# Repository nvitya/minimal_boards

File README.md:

# Breadboard Friendly Minimal Boards

The project on the Github: [https://github.com/nvitya/minimal_boards](https://github.com/nvitya/minimal_boards)

The boards are developed with KiCAD 5: [http://kicad.org/](http://kicad.org/)

## Board List

__Name__        | __Status__      | __Description__
----------------|-----------------|-------------------------------------------------------------
MIBO48-STM32    | Tested, OK      | For 48 pin QFP STM32 Microcontrollers (F103, F303, F070 etc)
MIBO48-STM32G4  | Tested, OK      | For 48 pin QFP STM32G4 Microcontrollers
MIBO48-XMC4     | Tested, OK      | For 48 pin QFP XMC4000 Microcontrollers
MIBO64-STM32    | Tested, OK      | For 64 pin QFP STM32 Microcontrollers (F405, F303, F070 etc)
MIBO64-ATSAM4S  | Tested, OK      | For 64 pin QFP ATSAM4SxB Microcontrollers
MIBO64-ATSAME5X | Tested, OK      | For 64 pin QFP ATSAME5xJ/ATSAMD5x Microcontrollers
MIBO20-STM32    | Tested, OK      | For the 20 pin TSSOP STM32 Microcontrollers (F030, F070, L011 etc)

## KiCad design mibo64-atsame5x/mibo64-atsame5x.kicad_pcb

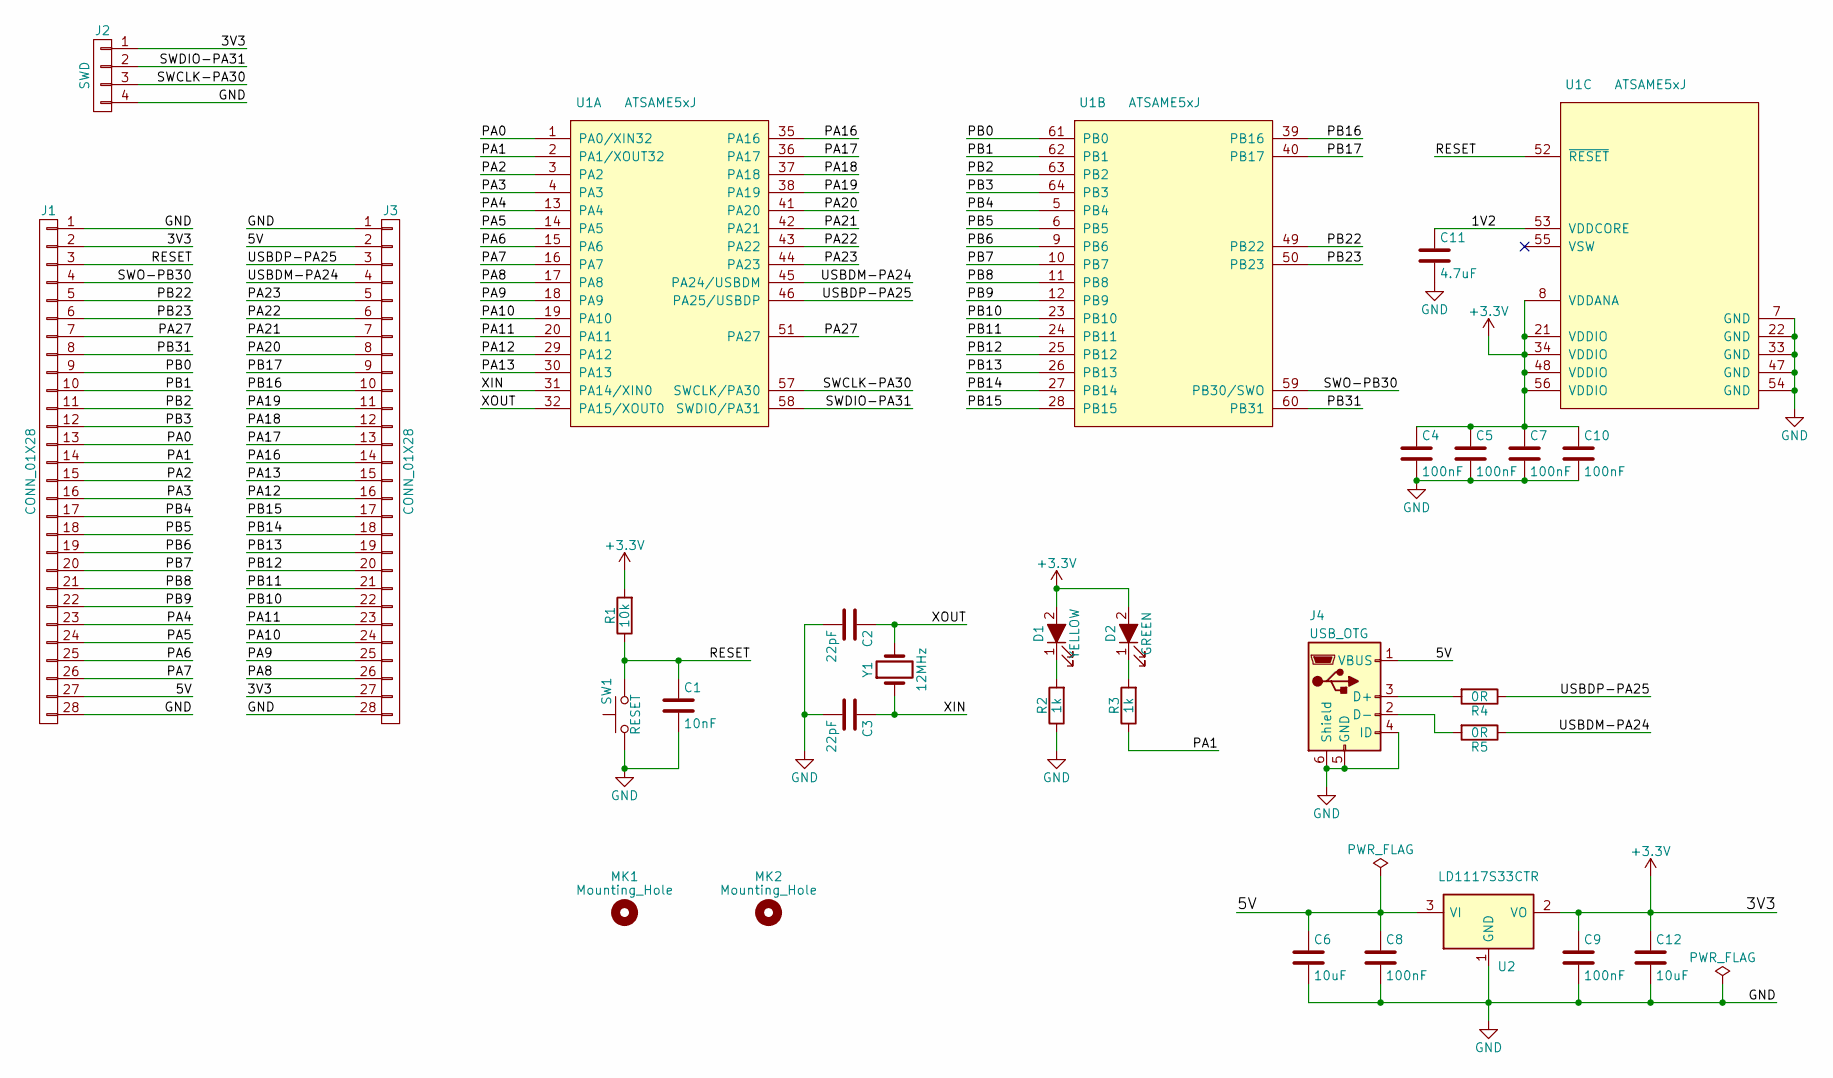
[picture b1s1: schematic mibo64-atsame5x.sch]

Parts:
C1: 10nF; C_0603_HandSoldering
C2, C3: 22pF; C_0603_HandSoldering
C4, C5, C7, C8, C9, C10: 100nF; C_0603_HandSoldering
C6, C12: 10uF; C_0603_HandSoldering
C11: 4.7uF; C_0603_HandSoldering
D1: YELLOW; LED_0603_HandSoldering
D2: GREEN; LED_0603_HandSoldering
J1, J3: CONN_01X28; Pin_Header_Straight_1x28_Pitch2.54mm
J2: SWD; Pin_Header_Straight_1x04_Pitch2.54mm
J4: USB_OTG; USB_Micro-B
MK1, MK2: Mounting_Hole; MountingHole_3.2mm_M3
R1: 10k; R_0603_HandSoldering
R2, R3: 1k; R_0603_HandSoldering
R4, R5: 0R; R_0603_HandSoldering
SW1: RESET; SW_SPST_FSMSM
U1: ATSAME5xJ; TQFP-64_10x10mm_Pitch0.5mm
U2: LD1117S33CTR; SOT-223
Y1: 12MHz; Crystal_HC49-4H_Vertical

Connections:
+3V3: C4.1, C5.1, C7.1, C9.1, C10.1, C12.1, D1.2 (A), D2.2 (A), J1.2, J2.1, J3.27, R1.2, U1.8 (VDDANA), U1.21 (VDDIO), U1.34 (VDDIO), U1.48 (VDDIO), U1.56 (VDDIO), U2.2 (VO)
/1V2: C11.1, U1.53 (VDDCORE)
/5V: C6.1, C8.1, J1.27, J3.2, J4.1 (VBUS), U2.3 (VI)
/PA0: J1.13, U1.1 (PA0/XIN32)
/PA1: J1.14, R3.1, U1.2 (PA1/XOUT32)
/PA2: J1.15, U1.3 (PA2)
/PA3: J1.16, U1.4 (PA3)
/PA4: J1.23, U1.13 (PA4)
/PA5: J1.24, U1.14 (PA5)
/PA6: J1.25, U1.15 (PA6)
/PA7: J1.26, U1.16 (PA7)
/PA8: J3.26, U1.17 (PA8)
/PA9: J3.25, U1.18 (PA9)
/PA10: J3.24, U1.19 (PA10)
/PA11: J3.23, U1.20 (PA11)
/PA12: J3.16, U1.29 (PA12)
/PA13: J3.15, U1.30 (PA13)
/PA16: J3.14, U1.35 (PA16)
/PA17: J3.13, U1.36 (PA17)
/PA18: J3.12, U1.37 (PA18)
/PA19: J3.11, U1.38 (PA19)
/PA20: J3.8, U1.41 (PA20)
/PA21: J3.7, U1.42 (PA21)
/PA22: J3.6, U1.43 (PA22)
/PA23: J3.5, U1.44 (PA23)
/PA27: J1.7, U1.51 (PA27)
/PB0: J1.9, U1.61 (PB0)
/PB1: J1.10, U1.62 (PB1)
/PB2: J1.11, U1.63 (PB2)
/PB3: J1.12, U1.64 (PB3)
/PB4: J1.17, U1.5 (PB4)
/PB5: J1.18, U1.6 (PB5)
/PB6: J1.19, U1.9 (PB6)
/PB7: J1.20, U1.10 (PB7)
/PB8: J1.21, U1.11 (PB8)
/PB9: J1.22, U1.12 (PB9)
/PB10: J3.22, U1.23 (PB10)
/PB11: J3.21, U1.24 (PB11)
/PB12: J3.20, U1.25 (PB12)
/PB13: J3.19, U1.26 (PB13)
/PB14: J3.18, U1.27 (PB14)
/PB15: J3.17, U1.28 (PB15)
/PB16: J3.10, U1.39 (PB16)
/PB17: J3.9, U1.40 (PB17)
/PB22: J1.5, U1.49 (PB22)
/PB23: J1.6, U1.50 (PB23)
/PB31: J1.8, U1.60 (PB31)
/RESET: C1.1, J1.3, R1.1, SW1.2, U1.52 (~RESET)
/SWCLK-PA30: J2.3, U1.57 (SWCLK/PA30)
/SWDIO-PA31: J2.2, U1.58 (SWDIO/PA31)
/SWO-PB30: J1.4, U1.59 (PB30/SWO)
/USBDM-PA24: J3.4, R5.1, U1.45 (PA24/USBDM)
/USBDP-PA25: J3.3, R4.1, U1.46 (PA25/USBDP)
/XIN: C3.1, U1.31 (PA14/XIN0), Y1.1
/XOUT: C2.1, U1.32 (PA15/XOUT0), Y1.2
GND: C1.2, C2.2, C3.2, C4.2, C5.2, C6.2, C7.2, C8.2, C9.2, C10.2, C11.2, C12.2, J1.1, J1.28, J2.4, J3.1, J3.28, J4.4 (ID), J4.5 (GND), J4.6 (Shield), R2.1, SW1.1, U1.7 (GND), U1.22 (GND), U1.33 (GND), U1.47 (GND), U1.54 (GND), U2.1 (GND)
unnamed: D1.1 (K), R2.2
unnamed: D2.1 (K), R3.2
unnamed: J4.2 (D-), R5.2
unnamed: J4.3 (D+), R4.2

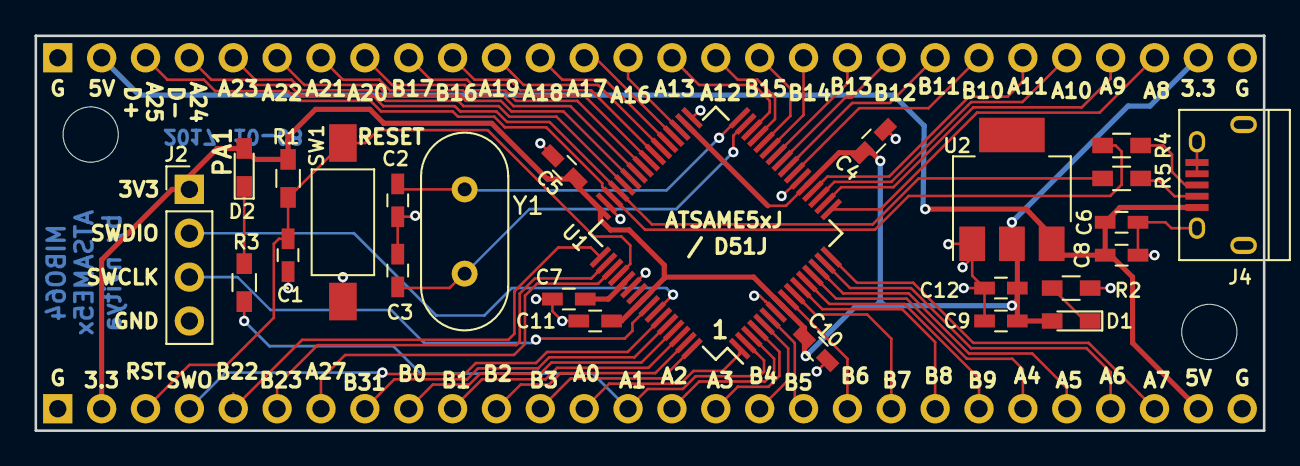
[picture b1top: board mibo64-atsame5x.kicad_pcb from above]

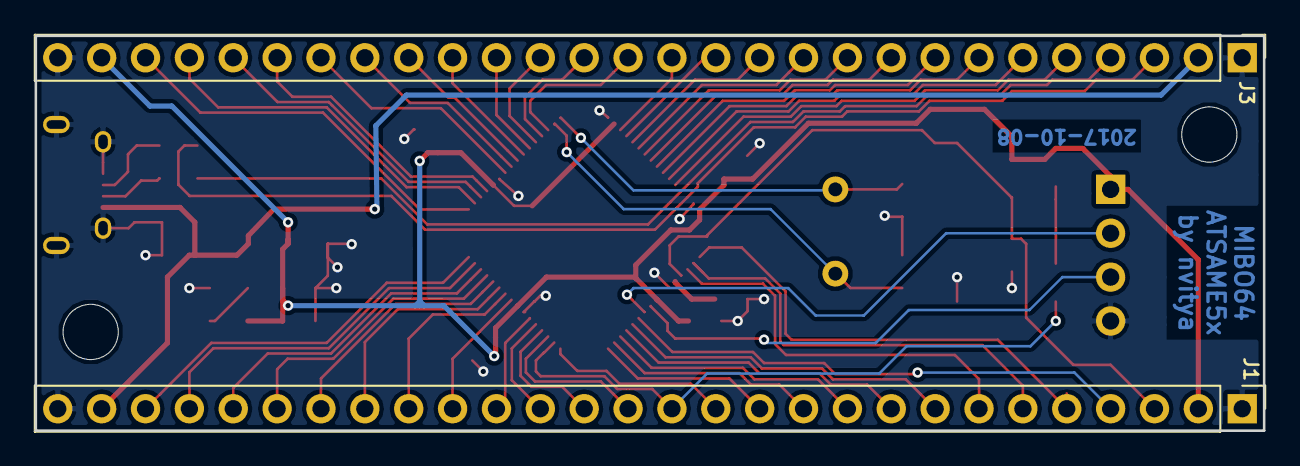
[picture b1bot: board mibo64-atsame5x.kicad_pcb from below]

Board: 2 copper layers, 71.1 x 22.9 mm, 29 parts (2 on the bottom side), 60 nets.

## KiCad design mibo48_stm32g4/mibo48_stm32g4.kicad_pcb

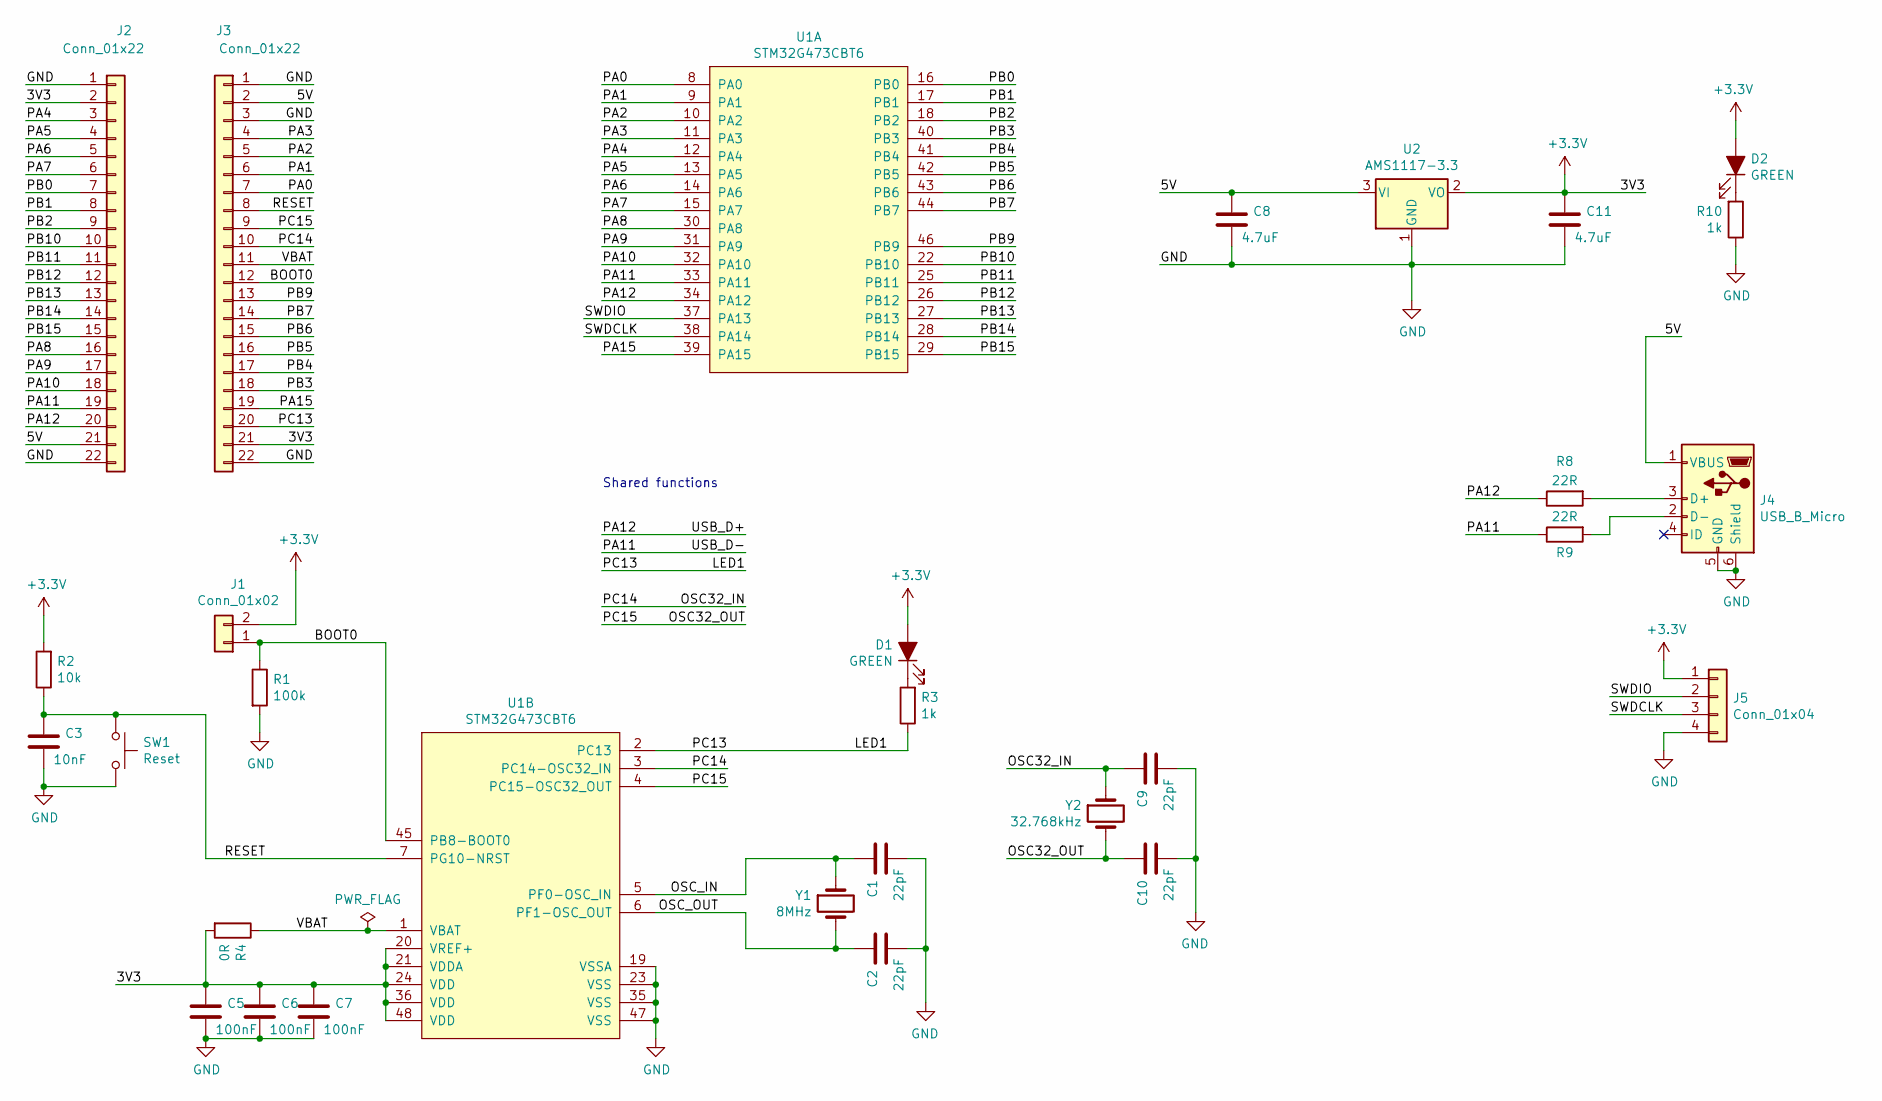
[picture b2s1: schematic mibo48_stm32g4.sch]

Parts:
C1, C2, C9, C10: 22pF; C_0603_1608Metric
C3: 10nF; C_0603_1608Metric
C5, C6, C7: 100nF; C_0603_1608Metric
C8, C11: 4.7uF; C_0603_1608Metric
D1, D2: GREEN; LED_0603_1608Metric
J1: Conn_01x02; PinHeader_1x02_P2.54mm_Vertical
J2, J3: Conn_01x22; PinHeader_1x22_P2.54mm_Vertical
J4: USB_B_Micro; USB_Micro-B_Molex-105017-0001
J5: Conn_01x04; PinHeader_1x04_P2.54mm_Vertical
R1: 100k; R_0603_1608Metric
R2: 10k; R_0603_1608Metric
R3, R10: 1k; R_0603_1608Metric
R4: 0R; R_0603_1608Metric
R8, R9: 22R; R_0603_1608Metric
SW1: Reset; SW_SPST_CK_RS282G05A3
U1: STM32G473CBT6; LQFP-48_7x7mm_P0.5mm
U2: AMS1117-3.3; SOT-223
Y1: 8MHz; Crystal_HC49-4H_Vertical
Y2: 32.768kHz; Crystal_C26-LF_D2.1mm_L6.5mm_Horizontal

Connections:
+3V3: C5.1, C6.1, C7.1, C11.1, D1.2 (A), D2.2 (A), J1.2, J2.2, J3.21, J5.1, R2.2, R4.2, U1.20 (VREF+), U1.21 (VDDA), U1.24 (VDD), U1.36 (VDD), U1.48 (VDD), U2.2 (VO)
/5V: C8.1, J2.21, J3.2, J4.1 (VBUS), U2.3 (VI)
/BOOT0: J1.1, J3.12, R1.1, U1.45 (PB8-BOOT0)
/LED1: J3.20, R3.1, U1.2 (PC13)
/OSC32_IN: C9.1, J3.10, U1.3 (PC14-OSC32_IN), Y2.1
/OSC32_OUT: C10.1, J3.9, U1.4 (PC15-OSC32_OUT), Y2.2
/OSC_IN: C1.1, U1.5 (PF0-OSC_IN), Y1.1
/OSC_OUT: C2.1, U1.6 (PF1-OSC_OUT), Y1.2
/PA0: J3.7, U1.8 (PA0)
/PA1: J3.6, U1.9 (PA1)
/PA2: J3.5, U1.10 (PA2)
/PA3: J3.4, U1.11 (PA3)
/PA4: J2.3, U1.12 (PA4)
/PA5: J2.4, U1.13 (PA5)
/PA6: J2.5, U1.14 (PA6)
/PA7: J2.6, U1.15 (PA7)
/PA8: J2.16, U1.30 (PA8)
/PA9: J2.17, U1.31 (PA9)
/PA10: J2.18, U1.32 (PA10)
/PA11: J2.19, R9.1, U1.33 (PA11)
/PA12: J2.20, R8.1, U1.34 (PA12)
/PA15: J3.19, U1.39 (PA15)
/PB0: J2.7, U1.16 (PB0)
/PB1: J2.8, U1.17 (PB1)
/PB2: J2.9, U1.18 (PB2)
/PB3: J3.18, U1.40 (PB3)
/PB4: J3.17, U1.41 (PB4)
/PB5: J3.16, U1.42 (PB5)
/PB6: J3.15, U1.43 (PB6)
/PB7: J3.14, U1.44 (PB7)
/PB9: J3.13, U1.46 (PB9)
/PB10: J2.10, U1.22 (PB10)
/PB11: J2.11, U1.25 (PB11)
/PB12: J2.12, U1.26 (PB12)
/PB13: J2.13, U1.27 (PB13)
/PB14: J2.14, U1.28 (PB14)
/PB15: J2.15, U1.29 (PB15)
/RESET: C3.1, J3.8, R2.1, SW1.1, U1.7 (PG10-NRST)
/SWDCLK: J5.3, U1.38 (PA14)
/SWDIO: J5.2, U1.37 (PA13)
/VBAT: J3.11, R4.1, U1.1 (VBAT)
GND: C1.2, C2.2, C3.2, C5.2, C6.2, C7.2, C8.2, C9.2, C10.2, C11.2, J2.1, J2.22, J3.1, J3.3, J3.22, J4.5 (GND), J4.6 (Shield), J5.4, R1.2, R10.1, SW1.2, U1.19 (VSSA), U1.23 (VSS), U1.35 (VSS), U1.47 (VSS), U2.1 (GND)
unnamed: D1.1 (K), R3.2
unnamed: D2.1 (K), R10.2
unnamed: J4.2 (D-), R9.2
unnamed: J4.3 (D+), R8.2

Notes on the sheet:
Shared functions

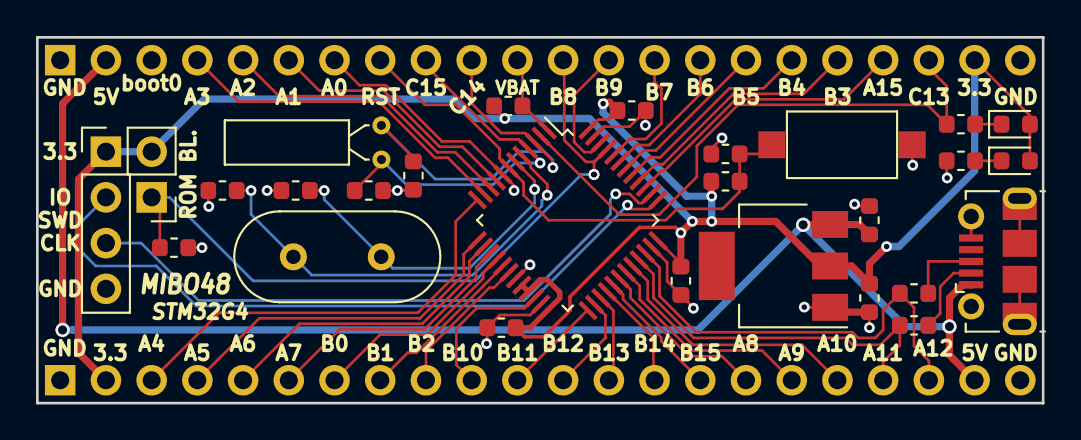
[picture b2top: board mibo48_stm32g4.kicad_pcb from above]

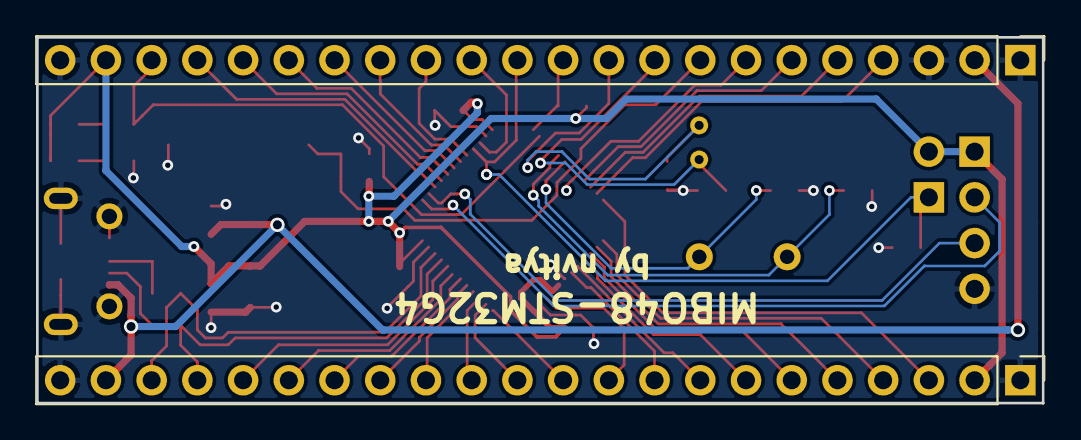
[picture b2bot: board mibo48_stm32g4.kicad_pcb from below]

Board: 2 copper layers, 55.9 x 20.3 mm, 29 parts (2 on the bottom side), 46 nets.

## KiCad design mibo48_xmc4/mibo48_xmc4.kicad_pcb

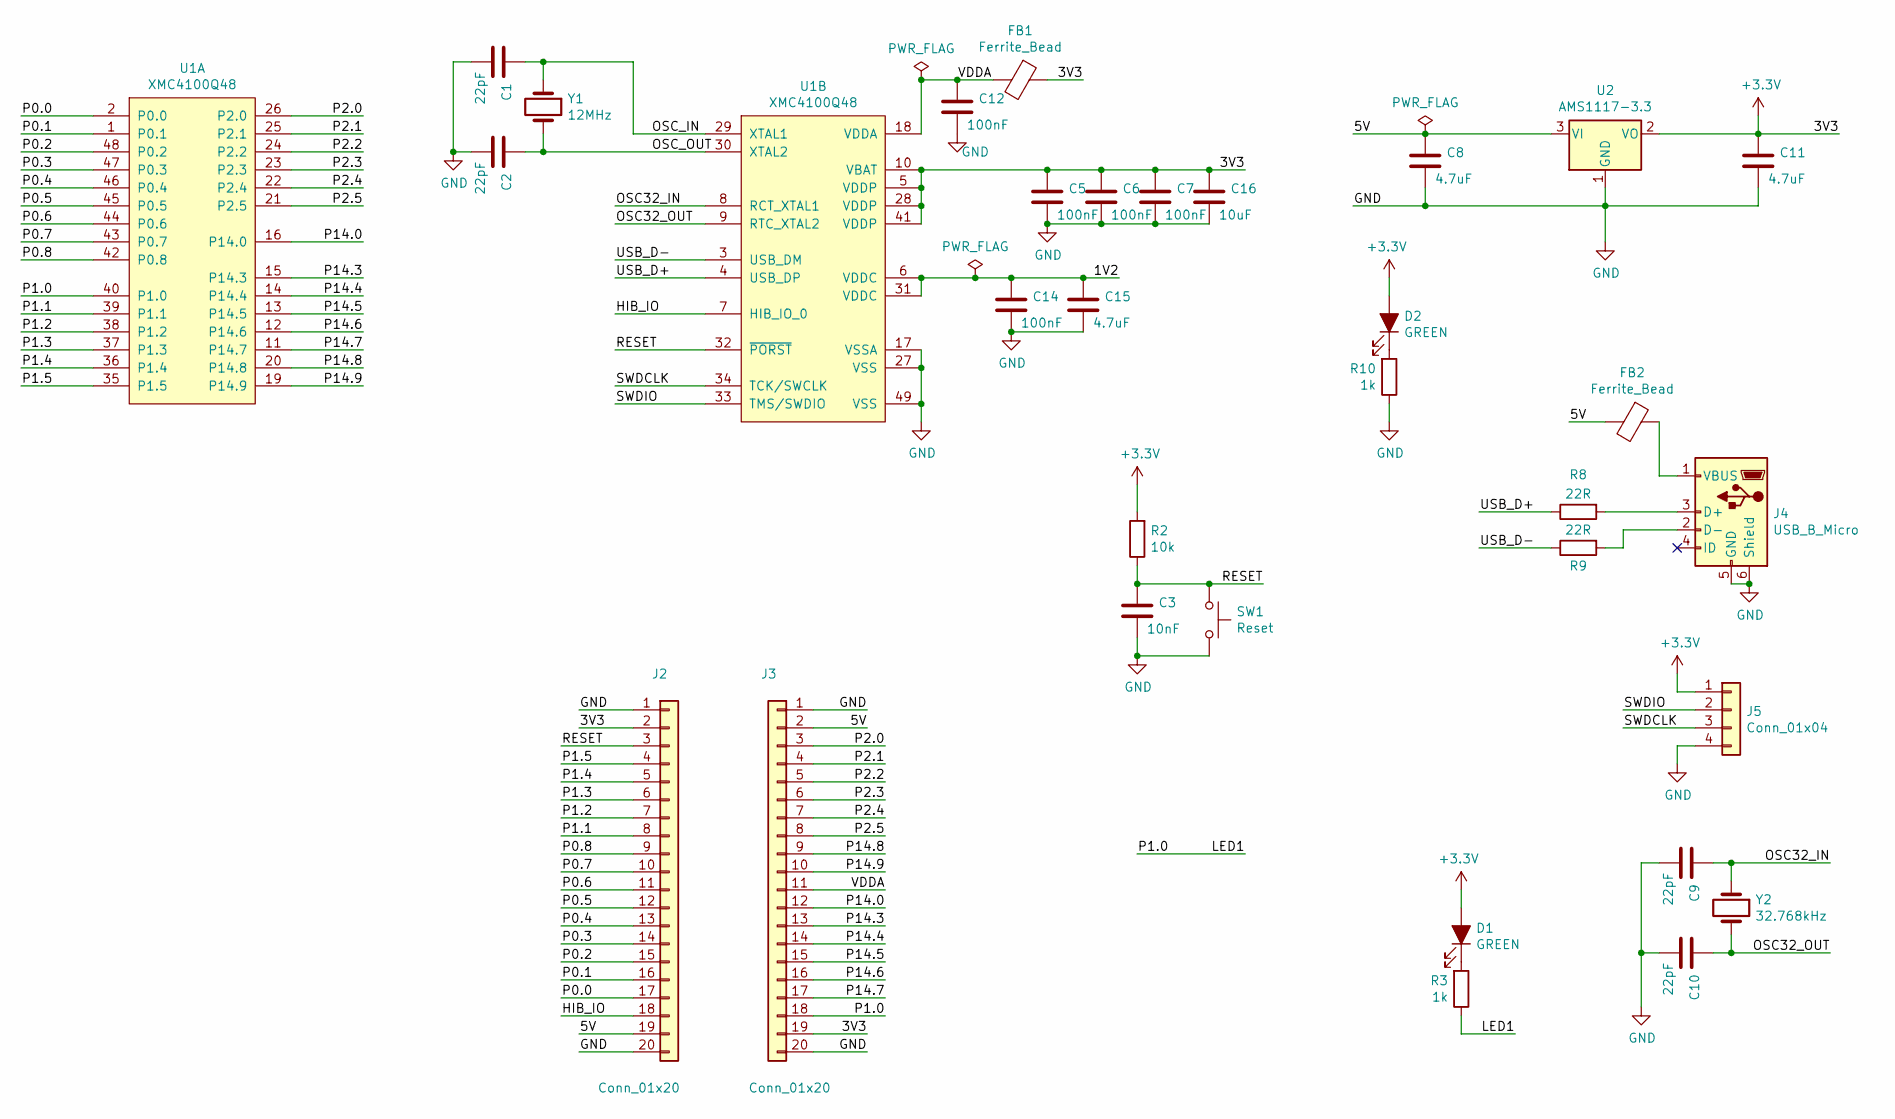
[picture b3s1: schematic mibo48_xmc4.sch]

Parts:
C1, C2, C9, C10: 22pF; C_0603_1608Metric
C3: 10nF; C_0603_1608Metric
C5, C6, C7, C12, C14: 100nF; C_0603_1608Metric
C8, C11: 4.7uF; C_1206_3216Metric
C15: 4.7uF; C_0603_1608Metric
C16: 10uF; C_0603_1608Metric
D1, D2: GREEN; LED_0603_1608Metric
FB1, FB2: Ferrite_Bead; L_0603_1608Metric
J2, J3: Conn_01x20; PinHeader_1x20_P2.54mm_Vertical
J4: USB_B_Micro; USB_Micro-B_Molex-105017-0001
J5: Conn_01x04; PinHeader_1x04_P2.54mm_Vertical
R2: 10k; R_0603_1608Metric
R3, R10: 1k; R_0603_1608Metric
R8, R9: 22R; R_0603_1608Metric
SW1: Reset; SW_SPST_CK_RS282G05A3
U1: XMC4100Q48; QFN-48-1EP_7x7mm_P0.5mm_EP5.3x5.3mm
U2: AMS1117-3.3; SOT-223-3_TabPin2
Y1: 12MHz; Crystal_HC49-4H_Vertical
Y2: 32.768kHz; Crystal_C26-LF_D2.1mm_L6.5mm_Horizontal

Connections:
+3V3: C5.1, C6.1, C7.1, C11.1, C16.1, D1.2 (A), D2.2 (A), FB1.1, J2.2, J3.19, J5.1, R2.2, U1.5 (VDDP), U1.10 (VBAT), U1.28 (VDDP), U1.41 (VDDP), U2.2 (VO)
/1V2: C14.1, C15.1, U1.6 (VDDC), U1.31 (VDDC)
/5V: C8.1, FB2.2, J2.19, J3.2, U2.3 (VI)
/HIB_IO: J2.18, U1.7 (HIB_IO_0)
/LED1: J3.18, R3.1, U1.40 (P1.0)
/OSC32_IN: C9.1, U1.8 (RCT_XTAL1), Y2.1
/OSC32_OUT: C10.1, U1.9 (RTC_XTAL2), Y2.2
/OSC_IN: C1.1, U1.29 (XTAL1), Y1.1
/OSC_OUT: C2.1, U1.30 (XTAL2), Y1.2
/P0.0: J2.17, U1.2 (P0.0)
/P0.1: J2.16, U1.1 (P0.1)
/P0.2: J2.15, U1.48 (P0.2)
/P0.3: J2.14, U1.47 (P0.3)
/P0.4: J2.13, U1.46 (P0.4)
/P0.5: J2.12, U1.45 (P0.5)
/P0.6: J2.11, U1.44 (P0.6)
/P0.7: J2.10, U1.43 (P0.7)
/P0.8: J2.9, U1.42 (P0.8)
/P1.1: J2.8, U1.39 (P1.1)
/P1.2: J2.7, U1.38 (P1.2)
/P1.3: J2.6, U1.37 (P1.3)
/P1.4: J2.5, U1.36 (P1.4)
/P1.5: J2.4, U1.35 (P1.5)
/P2.0: J3.3, U1.26 (P2.0)
/P2.1: J3.4, U1.25 (P2.1)
/P2.2: J3.5, U1.24 (P2.2)
/P2.3: J3.6, U1.23 (P2.3)
/P2.4: J3.7, U1.22 (P2.4)
/P2.5: J3.8, U1.21 (P2.5)
/P14.0: J3.12, U1.16 (P14.0)
/P14.3: J3.13, U1.15 (P14.3)
/P14.4: J3.14, U1.14 (P14.4)
/P14.5: J3.15, U1.13 (P14.5)
/P14.6: J3.16, U1.12 (P14.6)
/P14.7: J3.17, U1.11 (P14.7)
/P14.8: J3.9, U1.20 (P14.8)
/P14.9: J3.10, U1.19 (P14.9)
/RESET: C3.1, J2.3, R2.1, SW1.1, U1.32 (~PORST)
/SWDCLK: J5.3, U1.34 (TCK/SWCLK)
/SWDIO: J5.2, U1.33 (TMS/SWDIO)
/USB_D+: R8.1, U1.4 (USB_DP)
/USB_D-: R9.1, U1.3 (USB_DM)
/VDDA: C12.1, FB1.2, J3.11, U1.18 (VDDA)
GND: C1.2, C2.2, C3.2, C5.2, C6.2, C7.2, C8.2, C9.2, C10.2, C11.2, C12.2, C14.2, C15.2, C16.2, J2.1, J2.20, J3.1, J3.20, J4.5 (GND), J4.6 (Shield), J5.4, R10.1, SW1.2, U1.17 (VSSA), U1.27 (VSS), U1.49 (VSS), U2.1 (GND)
unnamed: D1.1 (K), R3.2
unnamed: D2.1 (K), R10.2
unnamed: FB2.1, J4.1 (VBUS)
unnamed: J4.2 (D-), R9.2
unnamed: J4.3 (D+), R8.2

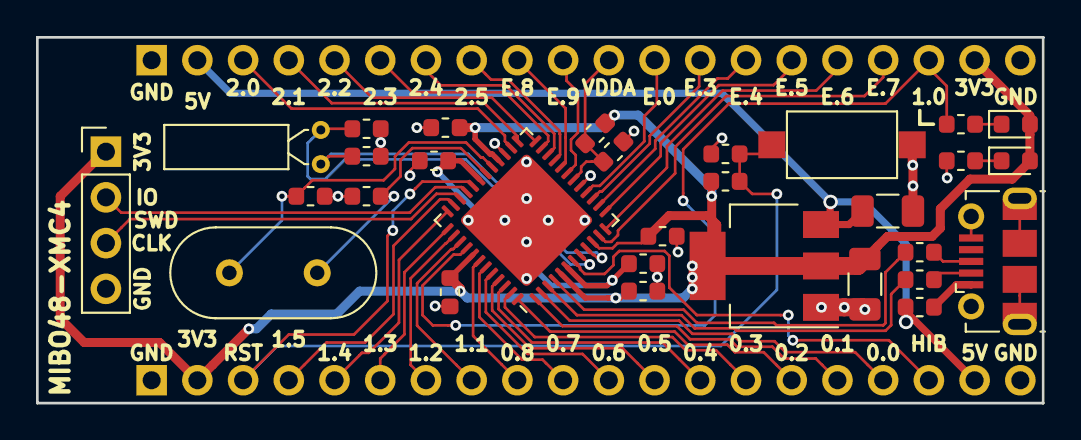
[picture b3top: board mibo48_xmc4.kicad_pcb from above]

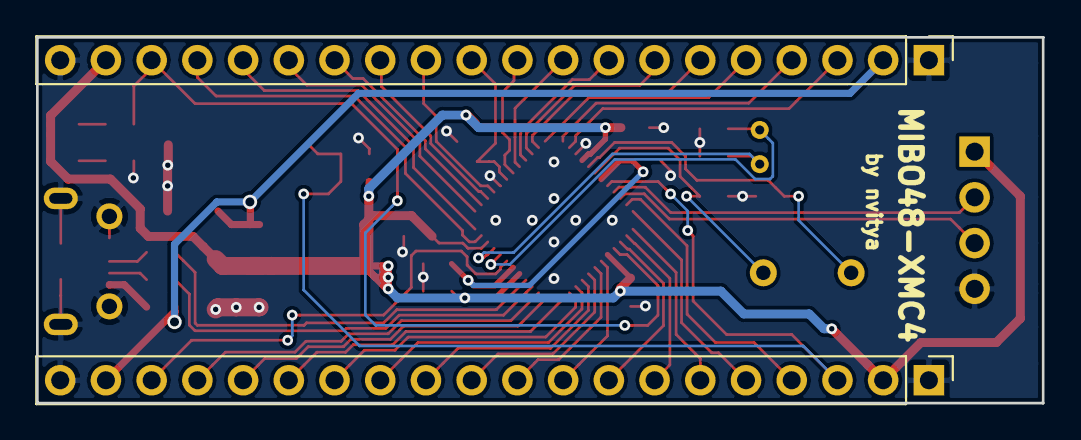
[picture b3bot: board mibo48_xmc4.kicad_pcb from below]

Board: 2 copper layers, 55.9 x 20.3 mm, 32 parts (2 on the bottom side), 49 nets.

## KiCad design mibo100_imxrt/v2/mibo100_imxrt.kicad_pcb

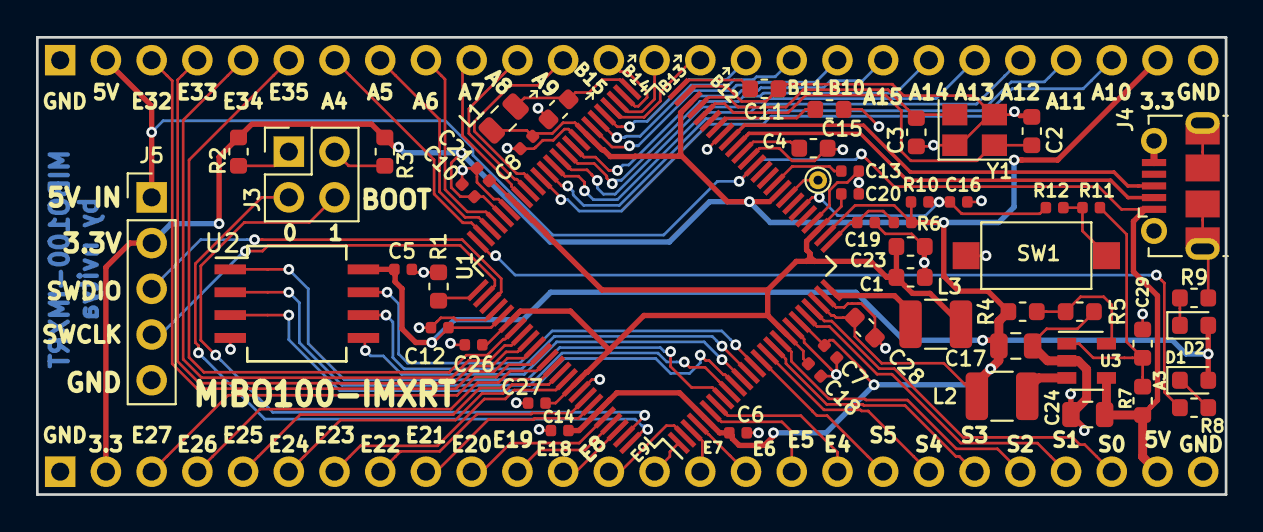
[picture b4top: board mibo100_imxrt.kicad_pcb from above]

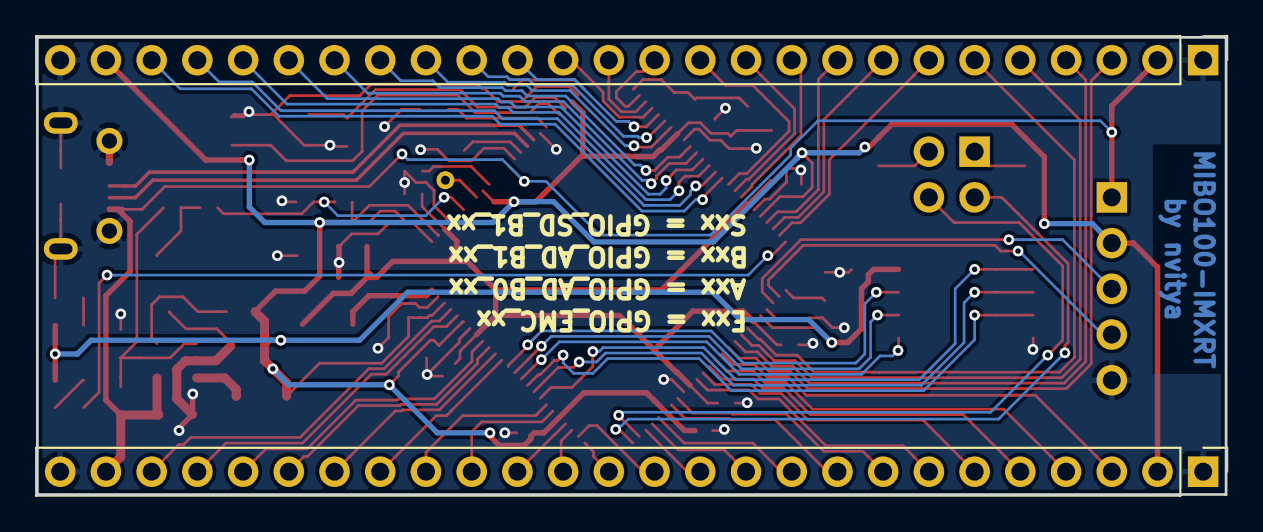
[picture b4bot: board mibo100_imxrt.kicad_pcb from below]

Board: 2 copper layers, 66.0 x 25.4 mm, 55 parts (2 on the bottom side), 81 nets.

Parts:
C1, C23: 22uF; C_0603_1608Metric
C2, C3: 22pF; C_0603_1608Metric
C4: 10uF; C_0603_1608Metric
C5, C6, C7, C8, C10, C12, C13, C14, C16, C18, C19, C20, C21, C26, C27: 220nF; C_0402_1005Metric
C9, C11, C15, C28: 4.7uF; C_0603_1608Metric
C17, C24: 4.7uF; C_0805_2012Metric
C29: 100nF; C_0603_1608Metric
D1, D2: GREEN; LED_0603_1608Metric
J1, J2: Conn_01x26; PinHeader_1x26_P2.54mm_Vertical
J3: Conn_02x02_Odd_Even; PinHeader_2x02_P2.54mm_Vertical
J4: USB_B_Micro; USB_Micro-B_Molex-105017-0001
J5: Conn_01x05; PinHeader_1x05_P2.54mm_Vertical
J6: Conn_01x01; TestPoint_THTPad_D1.0mm_Drill0.5mm
L1: 47nH; L_0805_2012Metric
L2: 2.2 uH; L_1210_3225Metric
L3: 4.7 uH; L_1210_3225Metric
R1, R2, R3, R7: 10k; R_0603_1608Metric
R4: 68k; R_0603_1608Metric
R5: 15k; R_0603_1608Metric
R6, R10: 30k; R_0402_1005Metric
R8, R9: 1k; R_0603_1608Metric
R11, R12: 0R; R_0402_1005Metric
SW1: SW_Push; SW_SPST_CK_RS282G05A3
U1: MIMXRT1021CAF4A; LQFP-100_14x14mm_P0.5mm
U2: W25X80; SO-8_5.3x6.2mm_P1.27mm
U3: AP3417C; SOT-23-5
Y1: 24MHz; Crystal_SMD_3225-4Pin_3.2x2.5mm

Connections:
+3V3: C5.1, C6.1, C7.1, C8.1, C10.1, C12.1, C14.1, C17.1, C28.1, D1.2, D2.2, J1.2, J2.25, J5.2, L1.1, L2.1, R2.2, R3.2, R4.2, R6.2, R10.2, U1.5, U1.20, U1.23, U1.27, U1.34, U1.48, U1.58, U1.71, U1.80, U1.95, U2.8
/3V3-EN: C29.1, R7.1, R11.1, U3.1
/5V: C24.1, J1.25, J2.2, J4.1, J5.1, R7.2, U1.38, U3.4
/A4: J2.7, U1.74
/A5: J2.8, U1.73
/A6: J2.9, U1.72
/A7: J2.10, U1.68
/A8: J2.11, U1.67
/A9: J2.12, U1.66
/A10: J2.24, U1.65
/A11: J2.23, U1.64
/A12: J2.22, U1.63
/A13: J2.21, U1.62
/A14: J2.20, U1.61
/A15: J2.19, U1.60
/B10: J2.18, U1.57
/B11: J2.17, U1.56
/B12: J2.16, U1.55
/B13: J2.15, U1.54
/B14: J2.14, U1.53
/B15: J2.13, U1.52
/BOOT-CFG-0: J3.3, U1.100
/BOOT-CFG-1: J3.4, U1.99
/DCDC_OUT: C1.1, C18.1, C20.1, C21.1, C23.1, C26.1, C27.1, L3.2, U1.18, U1.28, U1.69, U1.81, U1.91
/E4: J1.18, U1.7
/E5: J1.17, U1.6
/E6: J1.16, U1.4
/E7: J1.15, U1.3
/E8: J1.13, U1.2
/E9: J1.14, U1.1
/E18: J1.12, U1.98
/E19: J1.11, U1.97
/E20: J1.10, U1.96
/E21: J1.9, U1.94
/E22: J1.8, U1.93
/E23: J1.7, U1.90
/E24: J1.6, U1.89
/E25: J1.5, U1.88
/E26: J1.4, U1.87
/E27: J1.3, U1.86
/E32: J2.3, U1.85
/E33: J2.4, U1.84
/E34: J2.5, U1.83
/E35: J2.6, U1.82
/FLASH-CLK: U1.12, U2.6
/FLASH-CS: U1.8, U2.1
/FLASH-D0: U1.11, U2.5
/FLASH-D1: U1.9, U2.2
/FLASH-D2: U1.10, U2.3
/FLASH-D3: U1.13, U2.7
/JTAG-MOD: R1.2, U1.76
/LED1: R8.1, U1.75
/PMIC_ON: J6.1, U1.33
/POR_B: C16.1, R10.1, R12.2, U1.31
/S0: J1.24, U1.22
/S1: J1.23, U1.21
/S2: J1.22, U1.17
/S3: J1.21, U1.16
/S4: J1.20, U1.15
/S5: J1.19, U1.14
/SWDCLK: J5.4, U1.77
/SWDIO: J5.3, U1.78
/USB-D+: J4.3, U1.42
/USB-D-: J4.2, U1.41
/VDDA: C9.1, L1.2, U1.51
GND: C1.2, C2.2, C3.2, C4.2, C5.2, C6.2, C7.2, C8.2, C9.2, C10.2, C11.2, C12.2, C13.2, C14.2, C15.2, C16.2, C17.2, C18.2, C19.2, C20.2, C21.2, C23.2, C24.2, C26.2, C27.2, C28.2, C29.2, J1.1, J1.26, J2.1, J2.26, J4.5, J4.6, J5.5, R1.1, R5.1, R9.1, SW1.2, U1.19, U1.24, U1.29, U1.39, U1.43, U1.49, U1.59, U1.70, U1.79, U1.92, U2.4, U3.2, Y1.1, Y1.3
unnamed: C2.1, U1.46, Y1.2
unnamed: C3.1, U1.47, Y1.4
unnamed: C4.1, U1.40
unnamed: C11.1, U1.50
unnamed: C13.1, U1.35
unnamed: C15.1, U1.44
unnamed: C19.1, R6.1, U1.26
unnamed: D1.1, R8.2
unnamed: D2.1, R9.2
unnamed: J3.1, R2.1
unnamed: J3.2, R3.1
unnamed: L2.2, U3.3
unnamed: L3.1, U1.25
unnamed: R4.1, R5.2, U3.5
unnamed: R11.2, R12.1, SW1.1

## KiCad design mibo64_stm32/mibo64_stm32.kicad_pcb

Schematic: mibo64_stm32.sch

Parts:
C1, C2, C9, C10: 22pF; C_0603_1608Metric
C3: 10nF; C_0603_1608Metric
C4, C5, C6, C7, C14: 100nF; C_0603_1608Metric
C8, C11: 4.7uF; C_0603_1608Metric
C12, C13: 2.2uF; C_0603_1608Metric
D1, D2: GREEN; LED_0603_1608Metric
J1: Conn_01x02; PinHeader_1x02_P2.54mm_Vertical
J2, J3: Conn_01x29; PinHeader_1x29_P2.54mm_Vertical
J4: USB_B_Micro; USB_Micro-B_Molex-105017-0001
J5: Conn_01x04; PinHeader_1x04_P2.54mm_Vertical
R1: 100k; R_0603_1608Metric
R2: 10k; R_0603_1608Metric
R3, R10: 1k; R_0603_1608Metric
R4, R5, R6: 0R; R_0603_1608Metric
R7: 1.5k; R_0603_1608Metric
R8, R9: 22R; R_0603_1608Metric
SW1: Reset; SW_SPST_CK_RS282G05A3
U1: STM32F405RGTx; LQFP-64_10x10mm_P0.5mm
U2: AMS1117-3.3; SOT-223
Y1: 8MHz; Crystal_HC49-4H_Vertical
Y2: 32.768kHz; Crystal_C26-LF_D2.1mm_L6.5mm_Horizontal

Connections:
+3V3: C4.1, C5.1, C6.1, C7.1, C11.1, C14.1, D1.2, D2.2, J1.2, J2.2, J3.28, J5.1, R2.2, R4.2, U1.13, U1.19, U1.32, U1.48, U1.64, U2.2 (VO)
/5V: C8.1, J2.28, J3.2, J4.1, R6.1, U2.3 (VI)
/BOOT0: J1.1, J3.3, R1.1, U1.60
/LED1: J3.27, R3.1, U1.2
/OSC32_IN: C9.1, J3.4, U1.3, Y2.1
/OSC32_OUT: C10.1, J3.5, U1.4, Y2.2
/OSC_IN: C1.1, U1.5, Y1.1
/OSC_OUT: C2.1, U1.6, Y1.2
/PA0: J3.9, U1.14
/PA1: J3.8, U1.15
/PA2: J3.7, U1.16
/PA3: J2.3, U1.17
/PA4: J2.4, U1.20
/PA5: J2.5, U1.21
/PA6: J2.6, U1.22
/PA7: J2.7, U1.23
/PA8: J2.23, U1.41
/PA9: J2.24, U1.42
/PA10: J2.25, U1.43
/PA11: J2.26, R9.1, U1.44
/PA12: J2.27, R8.1, U1.45
/PA15: J3.26, R5.2, U1.50
/PB0: J2.10, U1.26
/PB1: J2.11, U1.27
/PB2: J2.14, U1.28
/PB3: J3.21, U1.55
/PB4: J3.20, U1.56
/PB5: J3.19, U1.57
/PB6: J3.18, U1.58
/PB7: J3.17, U1.59
/PB8: J3.15, U1.61
/PB9: J3.16, U1.62
/PB10: J2.13, U1.29
/PB11: J2.12, U1.30
/PB12: J2.15, U1.33
/PB13: J2.16, U1.34
/PB14: J2.17, U1.35
/PB15: J2.18, U1.36
/PC0: J3.13, U1.8
/PC1: J3.12, U1.9
/PC2: J3.11, U1.10
/PC3: J3.10, U1.11
/PC4: J2.8, U1.24
/PC5: J2.9, U1.25
/PC6: J2.19, U1.37
/PC7: J2.20, U1.38
/PC8: J2.21, U1.39
/PC9: J2.22, U1.40
/PC10: J3.25, U1.51
/PC11: J3.24, U1.52
/PC12: J3.23, U1.53
/PD2: J3.22, U1.54
/RESET: C3.1, J3.6, R2.1, SW1.1, U1.7
/SWDCLK: J5.3, U1.49
/SWDIO: J5.2, U1.46
/VBAT: J3.14, R4.1, U1.1
GND: C1.2, C2.2, C3.2, C4.2, C5.2, C6.2, C7.2, C8.2, C9.2, C10.2, C11.2, C12.2, C13.2, C14.2, J2.1, J2.29, J3.1, J3.29, J4.5, J4.6, J5.4, R1.2, R10.1, SW1.2, U1.12, U1.18, U1.63, U2.1 (GND)
unnamed: C12.1, U1.31
unnamed: C13.1, U1.47
unnamed: D1.1, R3.2
unnamed: D2.1, R10.2
unnamed: J4.2, R9.2
unnamed: J4.3, R7.1, R8.2
unnamed: R5.1, R6.2, R7.2

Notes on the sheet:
Shared functions
0 Ohm resistors on F0,F1,F2,F3 devices

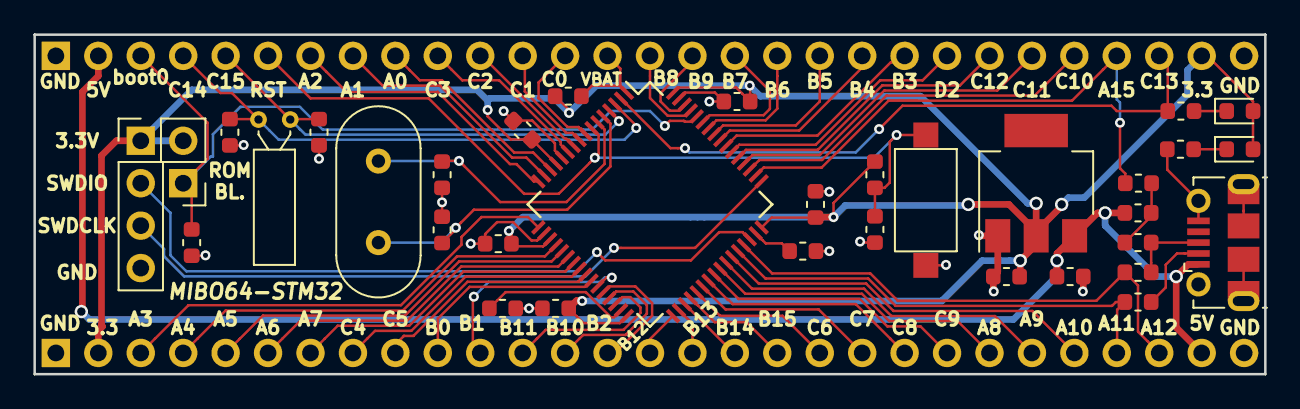
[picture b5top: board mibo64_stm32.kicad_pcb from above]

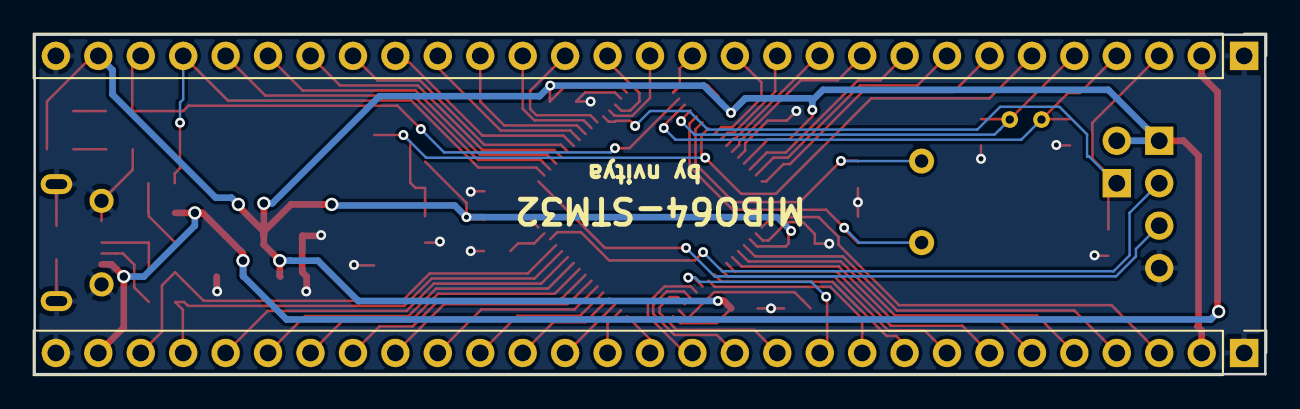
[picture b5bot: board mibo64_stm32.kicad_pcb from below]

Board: 2 copper layers, 73.7 x 20.3 mm, 36 parts (2 on the bottom side), 64 nets.

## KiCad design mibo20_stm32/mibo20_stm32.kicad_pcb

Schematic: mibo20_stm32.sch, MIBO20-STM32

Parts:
C1, C2: 22pF; C_0603_1608Metric
C3, C5: 100nF; C_0603_1608Metric
C4, C8, C9: 4.7uF; C_0603_1608Metric
C6: 10nF; C_0603_1608Metric
C7: 1uF; C_0603_1608Metric
D1: GREEN; LED_0603_1608Metric
D2: RED; LED_0603_1608Metric
J1: Conn_01x02; PinHeader_1x02_P2.54mm_Vertical
J2, J3: Conn_01x13; PinHeader_1x13_P2.54mm_Vertical
J4: USB_B_Micro; USB_Micro-B_Molex-105017-0001
J5: Conn_01x04; PinHeader_1x04_P2.54mm_Vertical
JP1, JP2: SolderJumper_2_Open; SolderJumper-2_P0.8mm_Open_RoundedPad0.6x0.8mm
R1: 100k; R_0603_1608Metric
R2: 10k; R_0603_1608Metric
R3, R4: 1k; R_0603_1608Metric
SW1: Reset; SW_SPST_CK_RS282G05A3
U1: STM32F070F6Px; TSSOP-20_4.4x6.5mm_P0.65mm
U2: AMS1117-3.3; SOT-223
Y1: 8MHz; Crystal_HC49-4H_Vertical

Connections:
+3V3: C4.1, C5.1, C6.1, C7.1, C9.1, J1.1, J2.2, J3.12, J5.1, R2.2, R3.2, R4.2, U1.5, U1.16, U2.2 (VO)
/5V: C8.1, J2.12, J3.2, J4.1, U2.3 (VI)
/BOOT0: J1.2, J3.5, R1.1, U1.1
/LED1: D1.1, J2.11, U1.14
/OSC_IN: C1.1, J3.4, U1.2, Y1.1
/OSC_OUT: C2.1, J3.3, U1.3, Y1.2
/PA0: J2.3, U1.6
/PA1: J2.4, U1.7
/PA2: J2.5, U1.8
/PA3: J2.6, U1.9
/PA4: J2.7, U1.10
/PA5: J2.8, U1.11
/PA6: J2.9, U1.12
/PA7: J2.10, U1.13
/PA10: J3.8, JP1.1, U1.18
/PA11: J3.7, JP2.1, U1.17
/PA13: J3.9, J5.2, U1.19
/PA14: J3.10, J5.3, U1.20
/RESET: C3.1, J3.6, R2.1, SW1.1, U1.4
GND: C1.2, C2.2, C3.2, C4.2, C5.2, C6.2, C7.2, C8.2, C9.2, D2.1, J2.1, J2.13, J3.1, J3.11, J3.13, J4.5, J4.6, J5.4, R1.2, SW1.2, U1.15, U2.1 (GND)
unnamed: D1.2, R3.1
unnamed: D2.2, R4.1
unnamed: J4.2, JP2.2
unnamed: J4.3, JP1.2

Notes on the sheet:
Shared functions

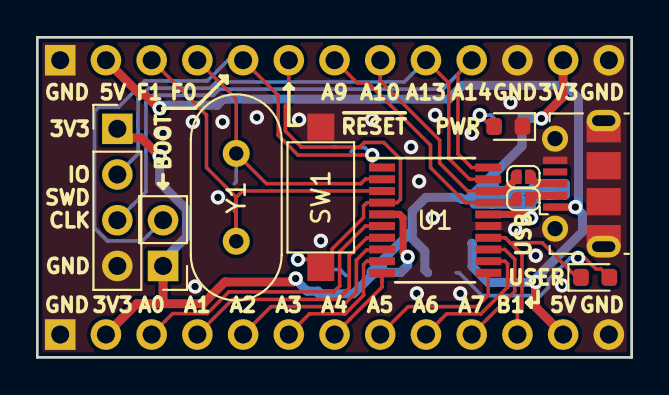
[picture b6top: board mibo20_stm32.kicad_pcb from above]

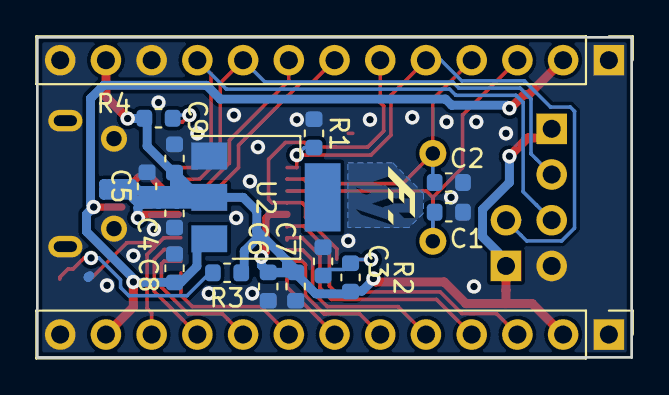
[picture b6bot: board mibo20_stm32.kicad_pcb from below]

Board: 2 copper layers, 33.0 x 17.8 mm, 26 parts (16 on the bottom side), 24 nets.
